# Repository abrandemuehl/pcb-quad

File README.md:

# UIUC ECE395 PCB Quadcopter Project
The goal of the project was to design a quadcopter with a PCB frame and as many
parts as possible soldered directly onto it. We put an STM32F4, and a BNO055 
IMU onto the board, and purchased external ESC's for the motors.

### Results
Due to difficulties with a parts order through the school, we were not able to 
sufficiently test the hardware before a final version was due. We missed a pull
up resistor on the BNO055's NRESET pin, causing it to constantly be in a state 
of reset, and making it unusable. We fixed it by taping our breakout board IMU 
onto the board, and connecting the necessary wires. After that, we had working 
hardware, but were not able to finish tuning the quadcopter before a failure 
broke one of the motors. We did not have a tuning rig, so we were forced to tune
it by attempting to hover at about floor level. Eventually, one of the motors 
that we used failed, ending the project with working hardware and software, but
incomplete tuning.

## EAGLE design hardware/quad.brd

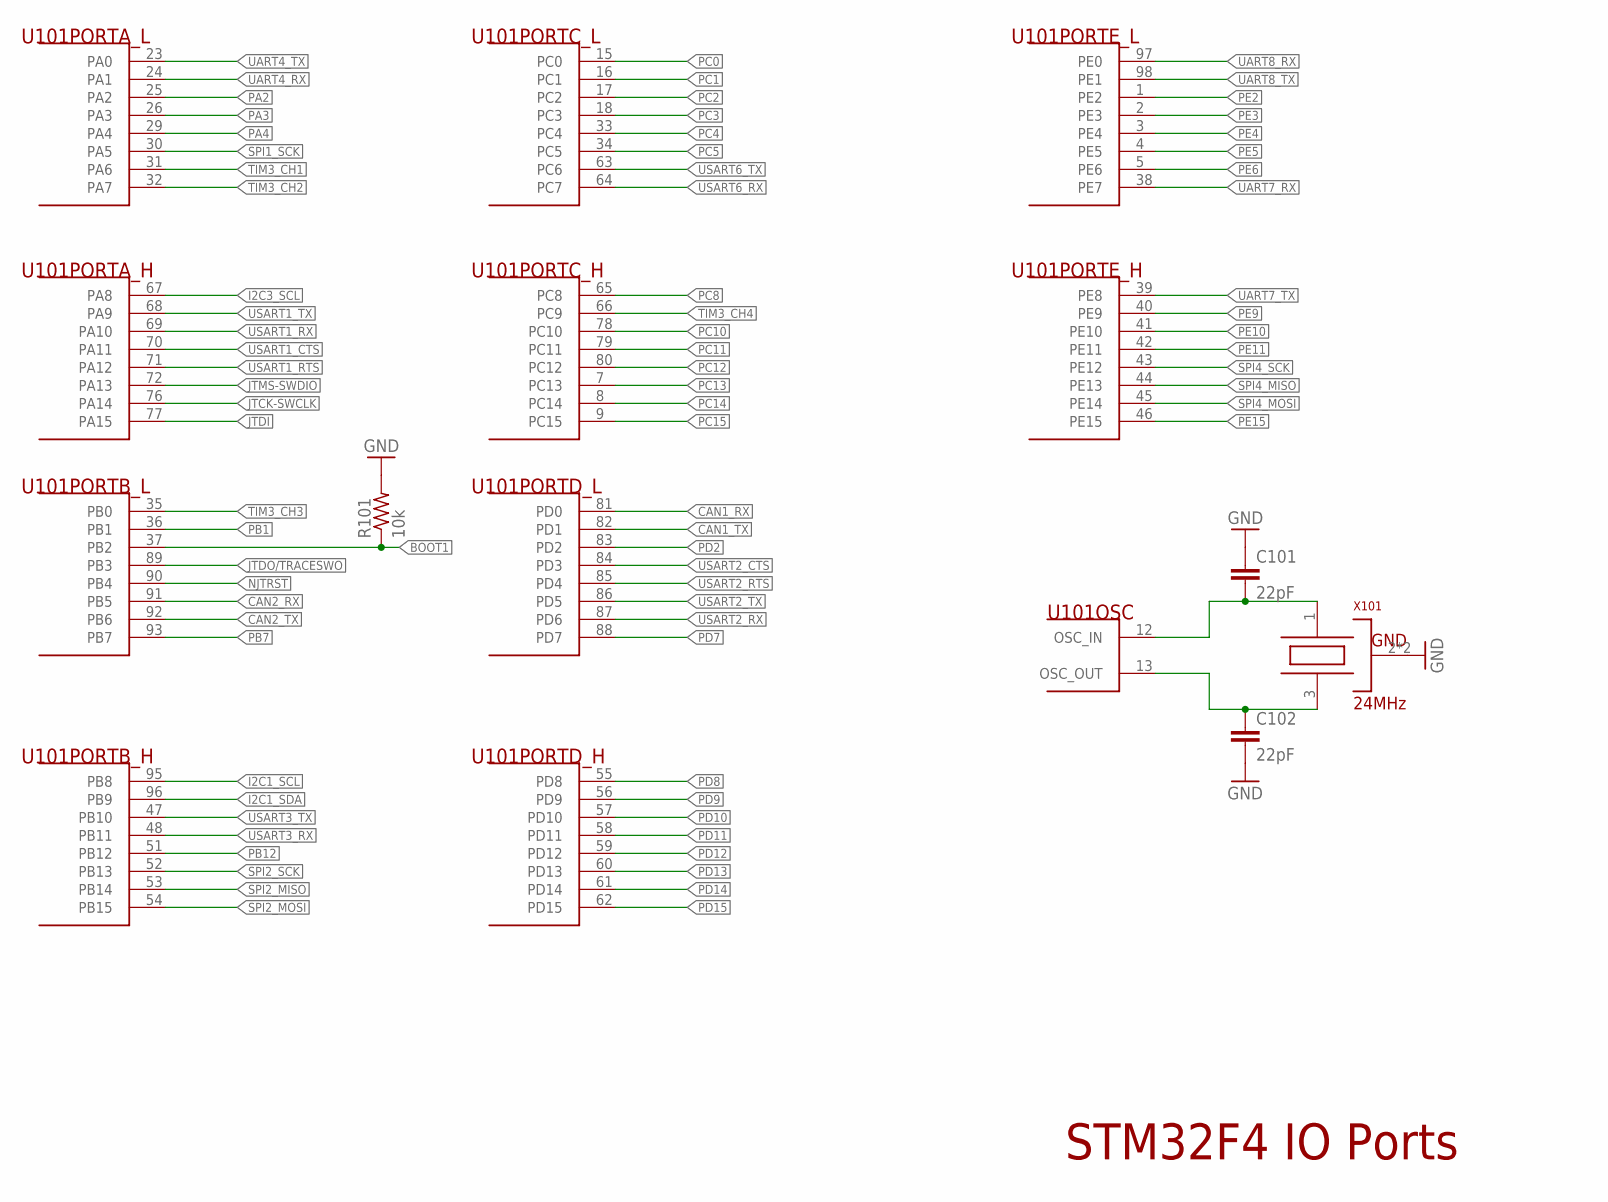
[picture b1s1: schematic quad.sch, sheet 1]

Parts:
C101, C102: 22pF; C0603
R101: 10k; R0603
U101: STM32F427VGT6; LQFP-100
X101: 24MHz; OSC3.2X2.5

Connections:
BOOT1: R101.1, U101.37 (PB2)
CAN1_RX: U101.81 (PD0)
CAN1_TX: U101.82 (PD1)
CAN2_RX: U101.91 (PB5)
CAN2_TX: U101.92 (PB6)
GND: C101.1, C102.2, R101.2, X101.2 (GND), X101.4 (GND); also elsewhere on the board
I2C1_SCL: U101.95 (PB8); also elsewhere on the board
I2C1_SDA: U101.96 (PB9); also elsewhere on the board
I2C3_SCL: U101.67 (PA8)
JTCK-SWCLK: U101.76 (PA14)
JTDI: U101.77 (PA15)
JTDO/TRACESWO: U101.89 (PB3)
JTMS-SWDIO: U101.72 (PA13)
NJTRST: U101.90 (PB4)
OSC_IN: C101.2, U101.12 (OSC_IN), X101.1 (OSC1)
OSC_OUT: C102.1, U101.13 (OSC_OUT), X101.3 (OSC2)
PA2: U101.25 (PA2)
PA3: U101.26 (PA3)
PA4: U101.29 (PA4)
PB1: U101.36 (PB1)
PB7: U101.93 (PB7)
PB12: U101.51 (PB12)
PC0: U101.15 (PC0)
PC1: U101.16 (PC1)
PC2: U101.17 (PC2)
PC3: U101.18 (PC3)
PC4: U101.33 (PC4)
PC5: U101.34 (PC5)
PC8: U101.65 (PC8)
PC10: U101.78 (PC10)
PC11: U101.79 (PC11)
PC12: U101.80 (PC12)
PC13: U101.7 (PC13)
PC14: U101.8 (PC14)
PC15: U101.9 (PC15)
PD2: U101.83 (PD2); also elsewhere on the board
PD7: U101.88 (PD7)
PD8: U101.55 (PD8)
PD9: U101.56 (PD9)
PD10: U101.57 (PD10)
PD11: U101.58 (PD11)
PD12: U101.59 (PD12)
PD13: U101.60 (PD13)
PD14: U101.61 (PD14)
PD15: U101.62 (PD15)
PE2: U101.1 (PE2)
PE3: U101.2 (PE3)
PE4: U101.3 (PE4)
PE5: U101.4 (PE5)
PE6: U101.5 (PE6)
PE9: U101.40 (PE9)
PE10: U101.41 (PE10)
PE11: U101.42 (PE11)
PE15: U101.46 (PE15)
SPI1_SCK: U101.30 (PA5)
SPI2_MISO: U101.53 (PB14)
SPI2_MOSI: U101.54 (PB15)
SPI2_SCK: U101.52 (PB13)
SPI4_MISO: U101.44 (PE13)
SPI4_MOSI: U101.45 (PE14)
SPI4_SCK: U101.43 (PE12)
TIM3_CH1: U101.31 (PA6); also elsewhere on the board
TIM3_CH2: U101.32 (PA7); also elsewhere on the board
TIM3_CH3: U101.35 (PB0); also elsewhere on the board
TIM3_CH4: U101.66 (PC9); also elsewhere on the board
UART4_RX: U101.24 (PA1)
UART4_TX: U101.23 (PA0)
UART7_RX: U101.38 (PE7)
UART7_TX: U101.39 (PE8)
UART8_RX: U101.97 (PE0)
UART8_TX: U101.98 (PE1)
USART1_CTS: U101.70 (PA11)
USART1_RTS: U101.71 (PA12)
USART1_RX: U101.69 (PA10); also elsewhere on the board
USART1_TX: U101.68 (PA9); also elsewhere on the board
USART2_CTS: U101.84 (PD3)
USART2_RTS: U101.85 (PD4)
USART2_RX: U101.87 (PD6)
USART2_TX: U101.86 (PD5)
USART3_RX: U101.48 (PB11); also elsewhere on the board
USART3_TX: U101.47 (PB10); also elsewhere on the board
USART6_RX: U101.64 (PC7)
USART6_TX: U101.63 (PC6)

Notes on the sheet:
STM32F4 IO Ports

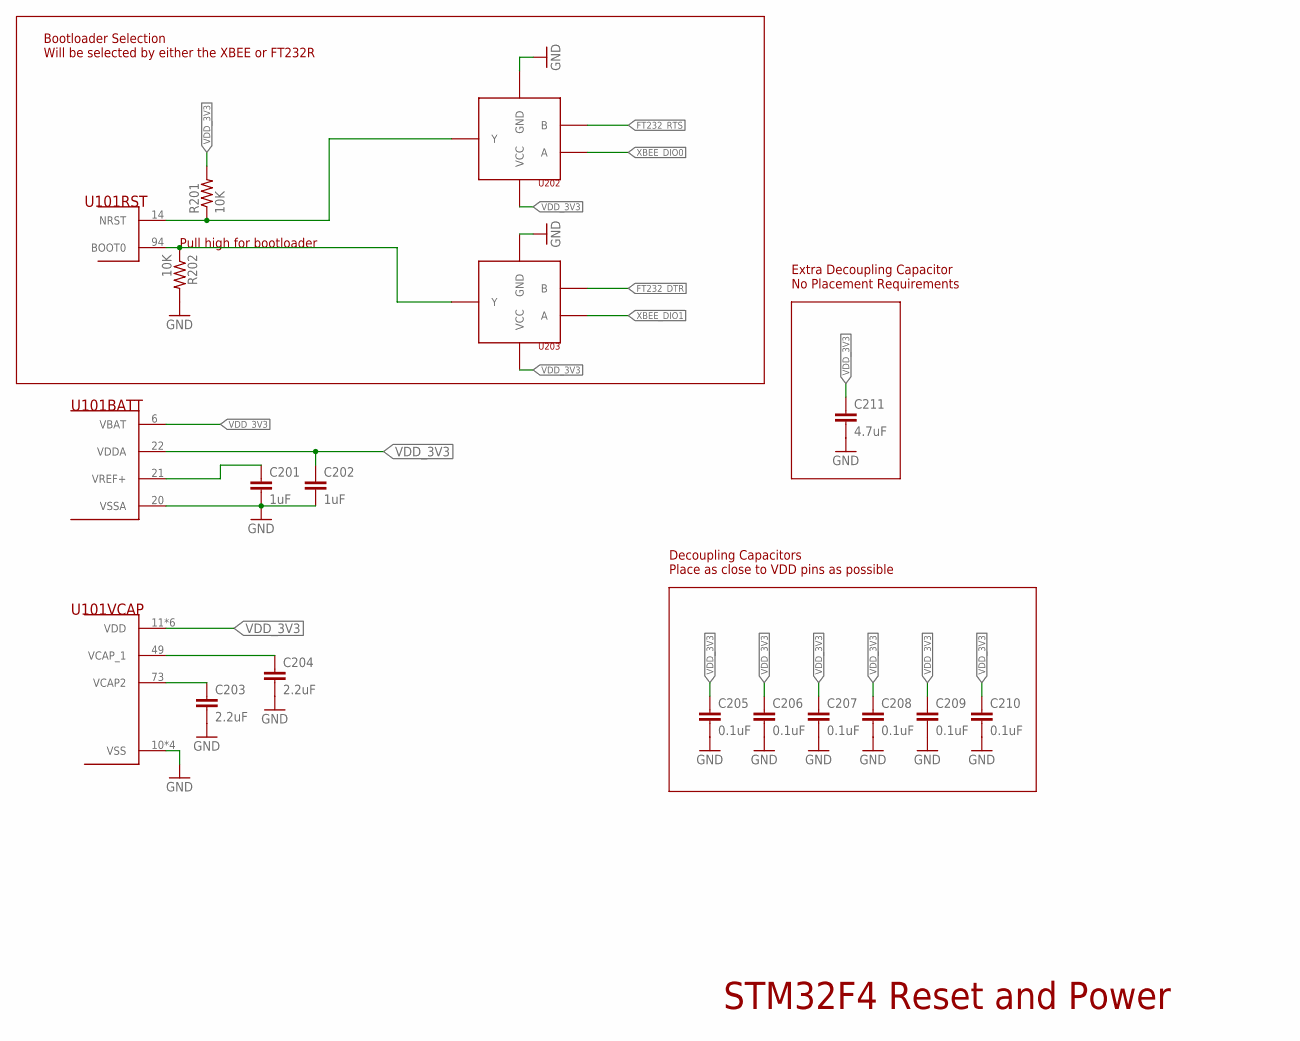
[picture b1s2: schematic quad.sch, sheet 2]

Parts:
C201, C202: 1uF; C0603
C203, C204: 2.2uF; C0603
C205, C206, C207, C208, C209, C210: 0.1uF; C0603
C211: 4.7uF; C0603
R201, R202: 10K; R0603
U101: STM32F427VGT6; LQFP-100
U202: AND_GATE; SOT23-5L
U203: SN74AHC1G32DBVR; SOT23-5L

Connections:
BOOT0: R202.1, U101.94 (BOOT0), U203.4 (Y)
FT232_DTR: U203.2 (B); also elsewhere on the board
FT232_RTS: U202.2 (B); also elsewhere on the board
GND: C201.2, C202.2, C203.2, C204.2, C205.2, C206.2, C207.2, C208.2, C209.2, C210.2, C211.2, R202.2, U101.10 (VSS), U101.20 (VSSA), U101.27 (VSS), U101.74 (VSS), U101.99 (VSS), U202.3 (GND), U203.3 (GND); also elsewhere on the board
NRST: R201.1, U101.14 (NRST), U202.4 (Y)
VCAP2: C203.1, U101.73 (VCAP2)
VCAP_1: C204.1, U101.49 (VCAP_1)
VDD_3V3: C201.1, C202.1, C205.1, C206.1, C207.1, C208.1, C209.1, C210.1, C211.1, R201.2, U101.6 (VBAT), U101.11 (VDD), U101.19 (VDD), U101.21 (VREF+), U101.22 (VDDA), U101.28 (VDD), U101.50 (VDD), U101.75 (VDD), U101.100 (VDD), U202.5 (VCC), U203.5 (VCC); also elsewhere on the board
XBEE_DIO0: U202.1 (A); also elsewhere on the board
XBEE_DIO1: U203.1 (A); also elsewhere on the board

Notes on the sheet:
STM32F4 Reset and Power
Decoupling Capacitors Place as close to VDD pins as possible
Extra Decoupling Capacitor No Placement Requirements
Pull high for bootloader
Bootloader Selection Will be selected by either the XBEE or FT232R

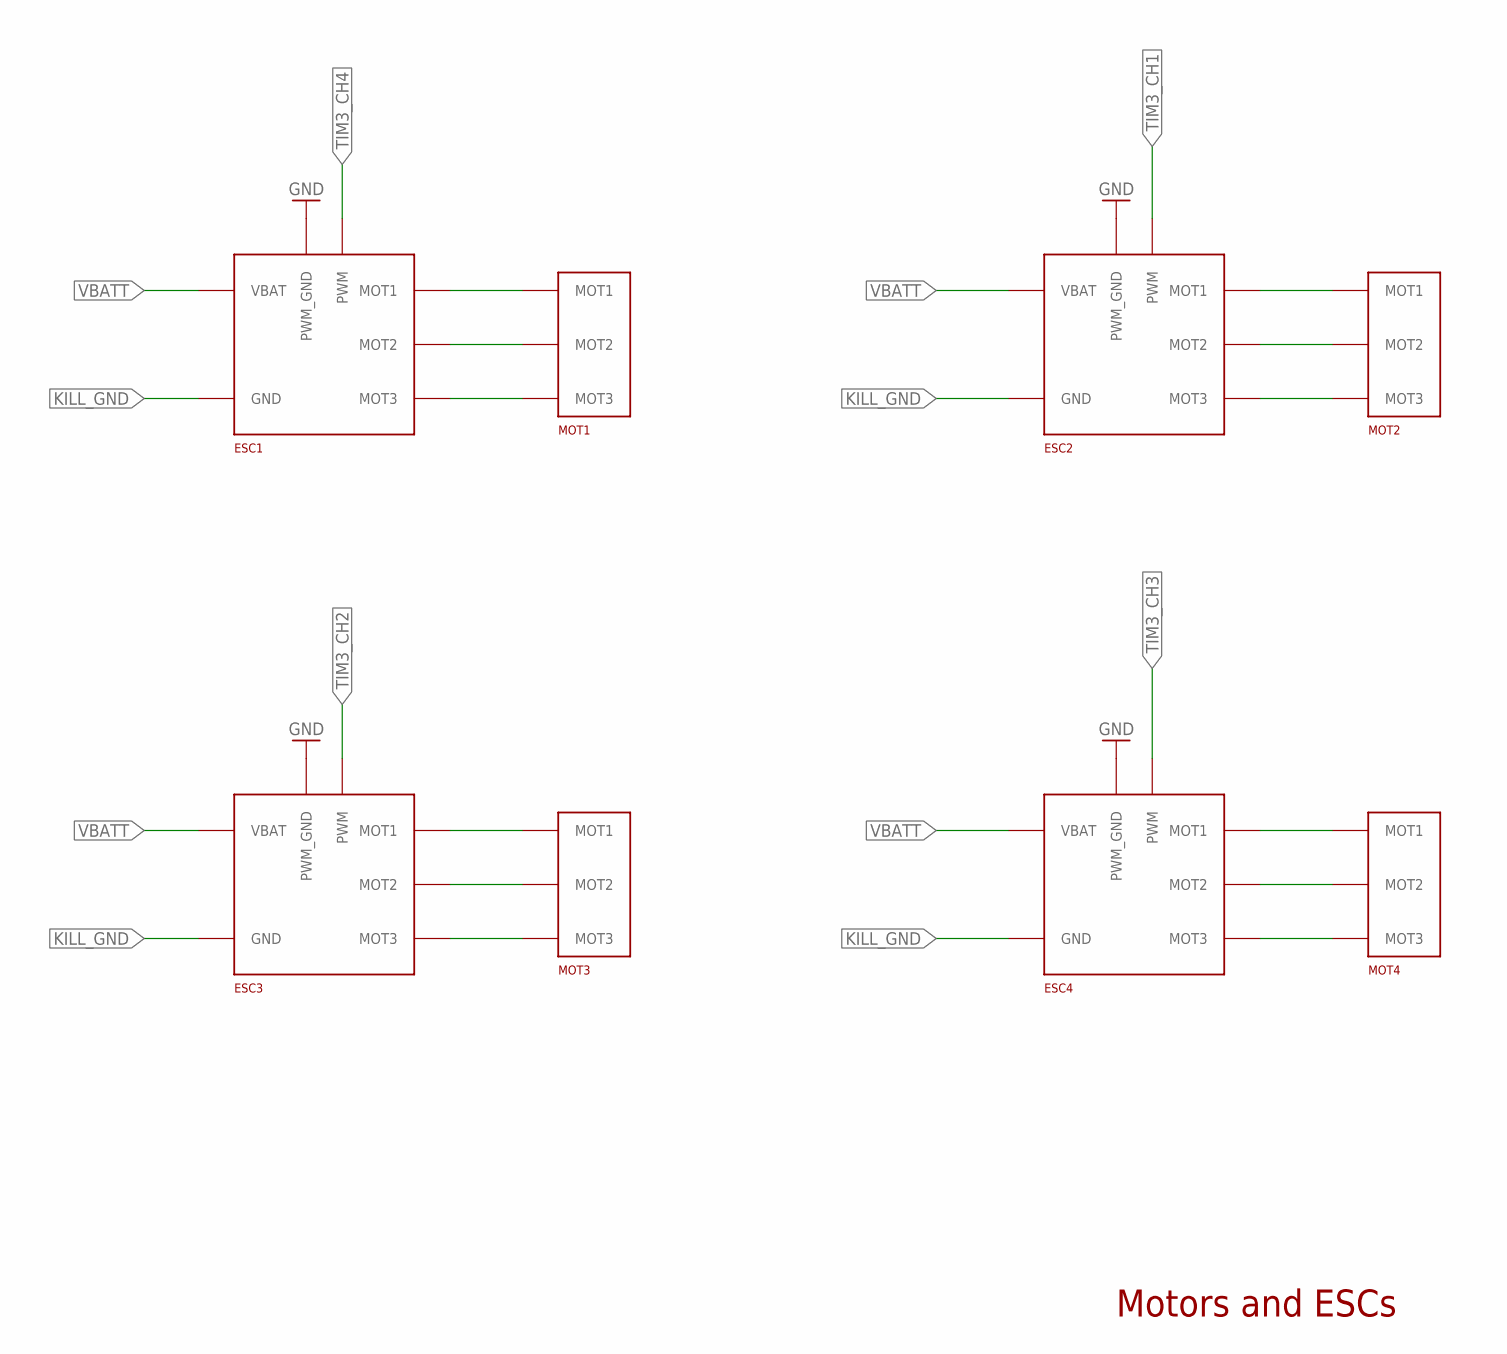
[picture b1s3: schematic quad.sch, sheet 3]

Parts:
ESC1, ESC2, ESC3, ESC4: AFRO_ESC
MOT1, MOT2, MOT3, MOT4: MOTOR

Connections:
GND: ESC1.PWM_GND, ESC2.PWM_GND, ESC3.PWM_GND, ESC4.PWM_GND; also elsewhere on the board
KILL_GND: ESC1.GND, ESC2.GND, ESC3.GND, ESC4.GND; also elsewhere on the board
MOT1_1: ESC1.MOT1, MOT1.MOT1
MOT1_2: ESC1.MOT2, MOT1.MOT2
MOT1_3: ESC1.MOT3, MOT1.MOT3
MOT2_1: ESC2.MOT1, MOT2.MOT1
MOT_2_2: ESC2.MOT2, MOT2.MOT2
MOT_2_3: ESC2.MOT3, MOT2.MOT3
MOT_3_1: ESC3.MOT1, MOT3.MOT1
MOT_3_2: ESC3.MOT2, MOT3.MOT2
MOT_3_3: ESC3.MOT3, MOT3.MOT3
MOT_4_1: ESC4.MOT1, MOT4.MOT1
MOT_4_2: ESC4.MOT2, MOT4.MOT2
MOT_4_3: ESC4.MOT3, MOT4.MOT3
TIM3_CH1: ESC2.PWM; also elsewhere on the board
TIM3_CH2: ESC3.PWM; also elsewhere on the board
TIM3_CH3: ESC4.PWM; also elsewhere on the board
TIM3_CH4: ESC1.PWM; also elsewhere on the board
VBATT: ESC1.VBATT (VBAT), ESC2.VBATT (VBAT), ESC3.VBATT (VBAT), ESC4.VBATT (VBAT); also elsewhere on the board

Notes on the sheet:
Motors and ESCs

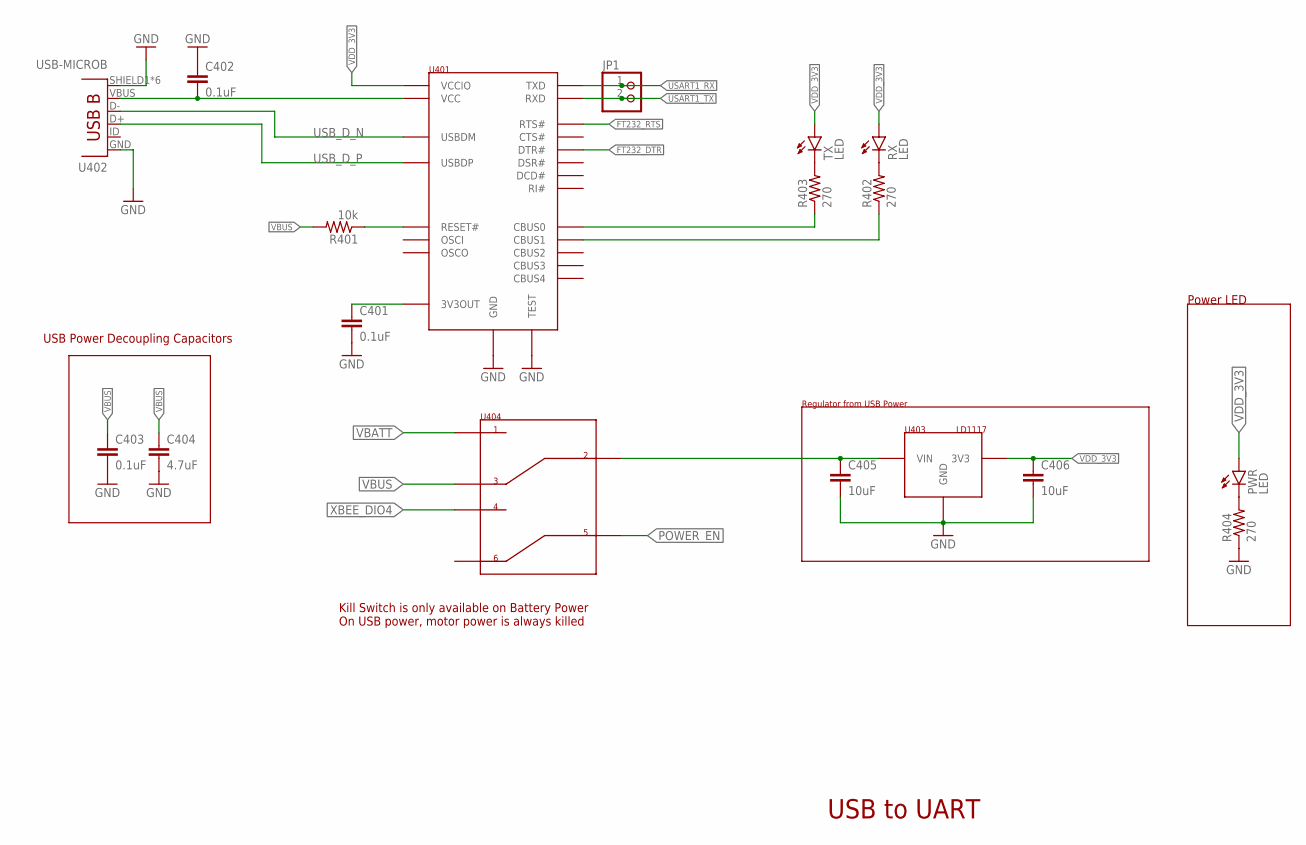
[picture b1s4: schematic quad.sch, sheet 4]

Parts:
C401, C402, C403: 0.1uF; C0603
C404: 4.7uF; C0603
C405, C406: 10uF; C0603
JP1: PINHD-1X2; 1X02
PWR: LED; LED-0603
R401: 10k; R0603
R402, R403, R404: 270; R0603
RX: LED; LED-0603
TX: LED; LED-0603
U401: FT232R; SSOP28
U402: USB-MICROB; USB-B-MICRO-SMD
U403: LD1117; SOT223
U404: MFS201N-16-Z

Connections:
FT232_DTR: U401.2 (DTR#); also elsewhere on the board
FT232_RTS: U401.3 (RTS#); also elsewhere on the board
GND: C401.2, C402.1, C403.2, C404.2, C405.2, C406.2, R404.1, U401.7 (GND), U401.18 (GND), U401.21 (GND), U401.25 (GND), U401.26 (TEST), U402.GND, U402.SHIELD1 (SHIELD), U402.SHIELD2 (SHIELD), U402.SHIELD3 (SHIELD), U402.SHIELD4 (SHIELD), U402.SHIELD5 (SHIELD), U402.SHIELD6 (SHIELD), U403.1 (GND); also elsewhere on the board
unnamed: R401.1, U401.19 (RESET#)
unnamed: C401.1, U401.17 (3V3OUT)
unnamed: R403.1, U401.23 (CBUS0)
unnamed: R402.1, U401.22 (CBUS1)
unnamed: R402.2, RX.C
unnamed: R403.2, TX.C
unnamed: PWR.C, R404.2
POWER_EN: U404.5; also elsewhere on the board
PWR: C405.1, U403.3 (VIN), U404.2
USART1_RX: JP1.1, U401.1 (TXD); also elsewhere on the board
USART1_TX: JP1.2, U401.5 (RXD); also elsewhere on the board
USB_D_N: U401.16 (USBDM), U402.D-
USB_D_P: U401.15 (USBDP), U402.D+
VBATT: U404.1; also elsewhere on the board
VBUS: C402.2, C403.1, C404.1, R401.2, U401.20 (VCC), U402.VBUS, U404.3
VDD_3V3: C406.1, PWR.A, RX.A, TX.A, U401.4 (VCCIO), U403.2 (3V3), U403.4 (3V3); also elsewhere on the board
XBEE_DIO4: U404.4; also elsewhere on the board

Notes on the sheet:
USB to UART
USB Power Decoupling Capacitors
Regulator from USB Power
Kill Switch is only available on Battery Power On USB power, motor power is always killed
Power LED

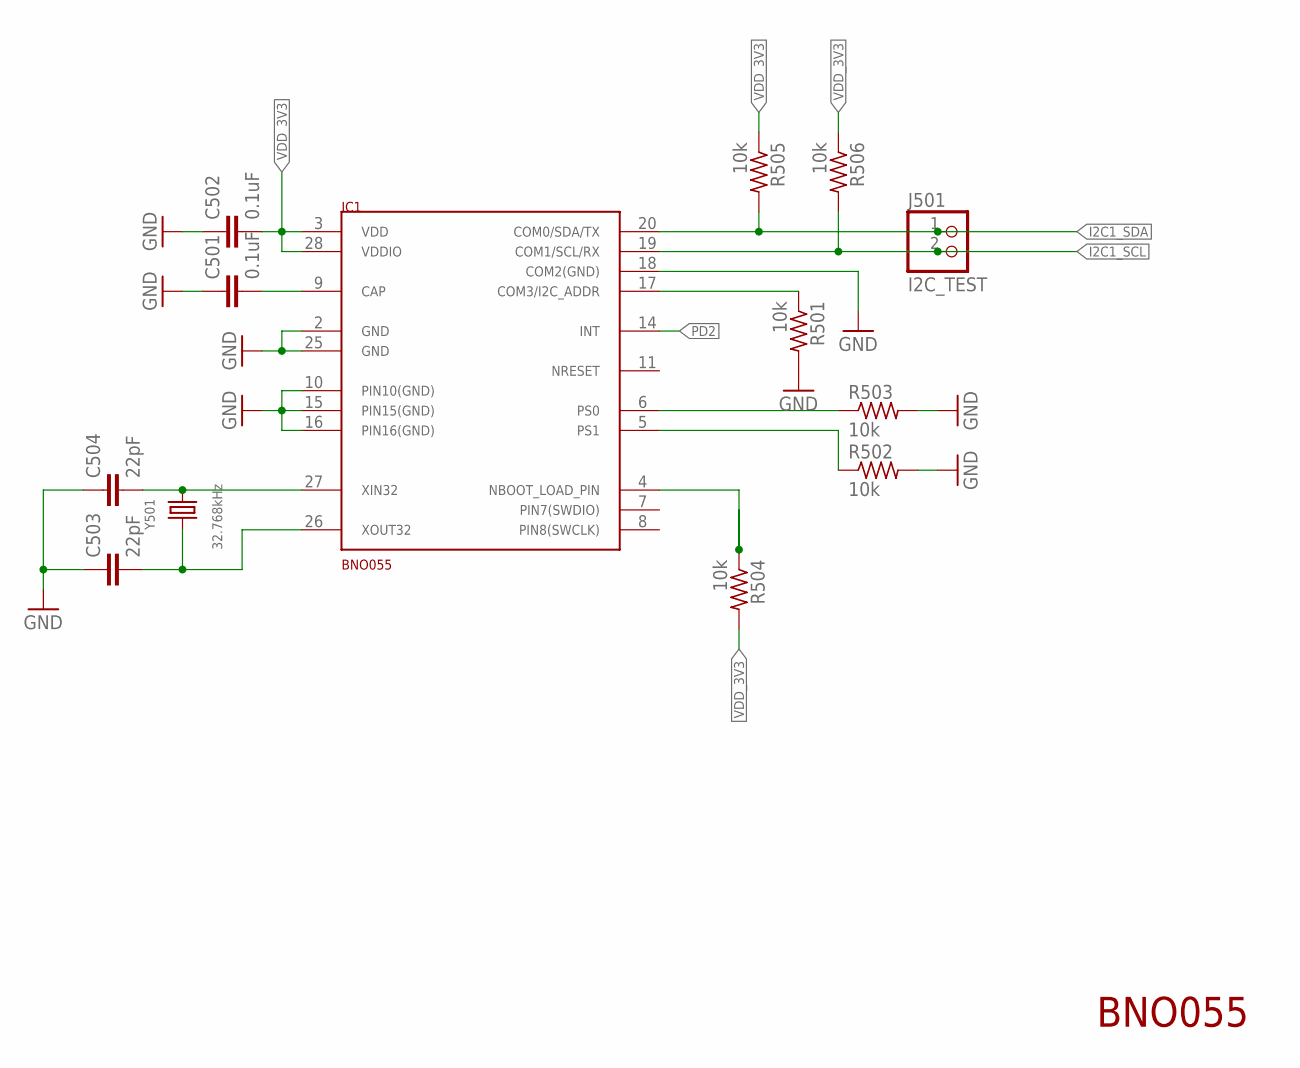
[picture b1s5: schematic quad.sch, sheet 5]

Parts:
C501, C502: 0.1uF; C0603
C503, C504: 22pF; C0603
IC1: BNO055; LGA-28_3.80X5.20/0.5
J501: I2C_TEST; 1X02
R501, R502, R503, R504, R505, R506: 10k; R0603
Y501: 32.768kHz; ABS25

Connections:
GND: C501.1, C502.1, C503.1, C504.1, IC1.2, IC1.10, IC1.15, IC1.16, IC1.18, IC1.25, R501.2, R502.2, R503.2; also elsewhere on the board
I2C1_SCL: IC1.19, J501.2, R506.2; also elsewhere on the board
I2C1_SDA: IC1.20, J501.1, R505.2; also elsewhere on the board
unnamed: C501.2, IC1.9
unnamed: C504.2, IC1.27, Y501.4 (2)
unnamed: C503.2, IC1.26, Y501.1
unnamed: IC1.17, R501.1
unnamed: IC1.6, R503.1
unnamed: IC1.5, R502.1
unnamed: IC1.4, R504.1
PD2: IC1.14; also elsewhere on the board
VDD_3V3: C502.2, IC1.3, IC1.28, R504.2, R505.1, R506.1; also elsewhere on the board

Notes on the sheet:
BNO055

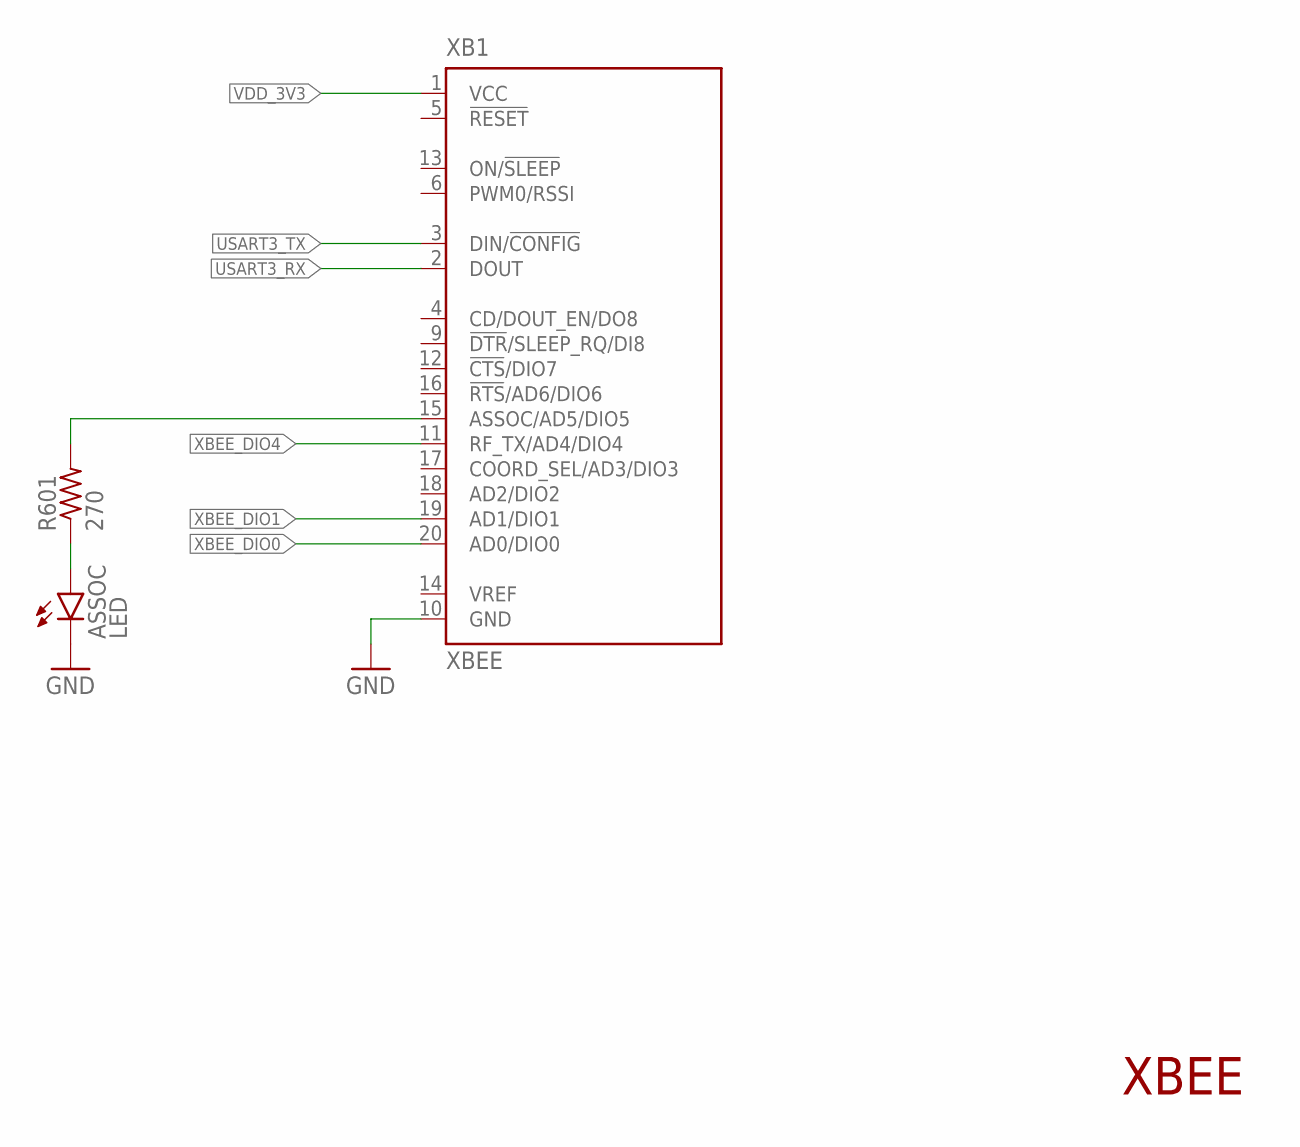
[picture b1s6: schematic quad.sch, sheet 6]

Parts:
ASSOC: LED; LED-0603
R601: 270; R0603
XB1: XBEE

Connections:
GND: ASSOC.C, XB1.10 (GND); also elsewhere on the board
unnamed: ASSOC.A, R601.1
unnamed: R601.2, XB1.15 (ASSOC/AD5/DIO5)
USART3_RX: XB1.2 (DOUT); also elsewhere on the board
USART3_TX: XB1.3 (DIN/!CONFIG); also elsewhere on the board
VDD_3V3: XB1.1 (VCC); also elsewhere on the board
XBEE_DIO0: XB1.20 (AD0/DIO0); also elsewhere on the board
XBEE_DIO1: XB1.19 (AD1/DIO1); also elsewhere on the board
XBEE_DIO4: XB1.11 (RF_TX/AD4/DIO4); also elsewhere on the board

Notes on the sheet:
XBEE

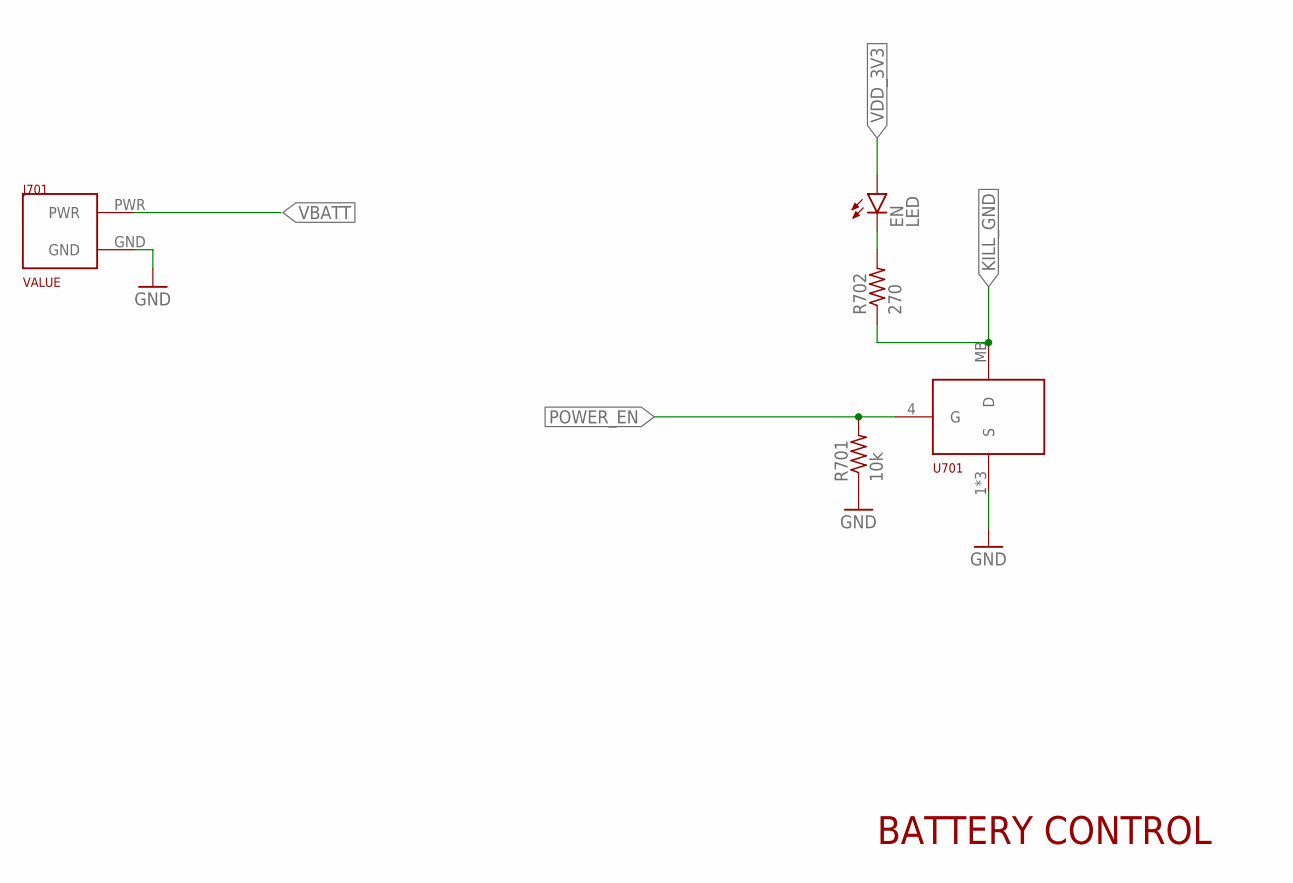
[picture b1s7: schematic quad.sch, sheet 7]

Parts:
EN: LED; LED-0603
J701: XT60
R701: 10k; R0603
R702: 270; R0603
U701: PSMN9RS-30YLC; SOT669

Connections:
GND: J701.GND, R701.1, U701.1 (S), U701.2 (S), U701.3 (S); also elsewhere on the board
KILL_GND: R702.1, U701.MB (D); also elsewhere on the board
unnamed: EN.C, R702.2
POWER_EN: R701.2, U701.4 (G); also elsewhere on the board
VBATT: J701.PWR; also elsewhere on the board
VDD_3V3: EN.A; also elsewhere on the board

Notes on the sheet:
BATTERY CONTROL

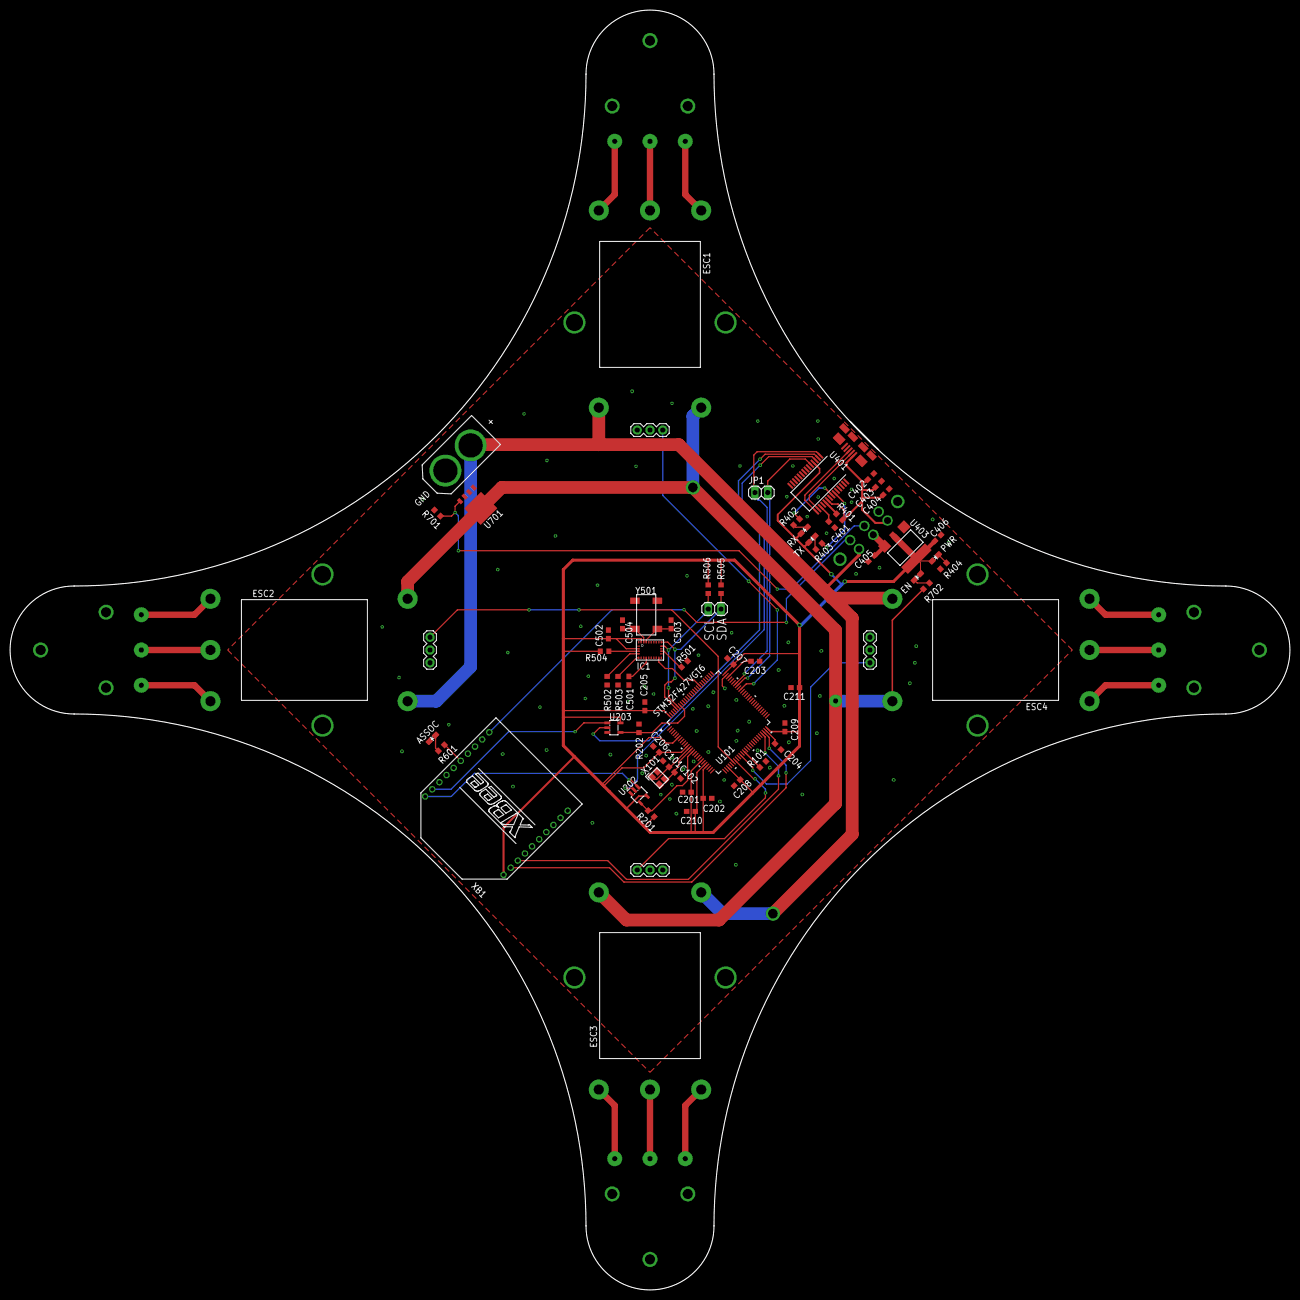
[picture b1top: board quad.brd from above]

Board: 2 copper layers, 254.0 x 254.0 mm, 67 parts (0 on the bottom side), 61 nets.

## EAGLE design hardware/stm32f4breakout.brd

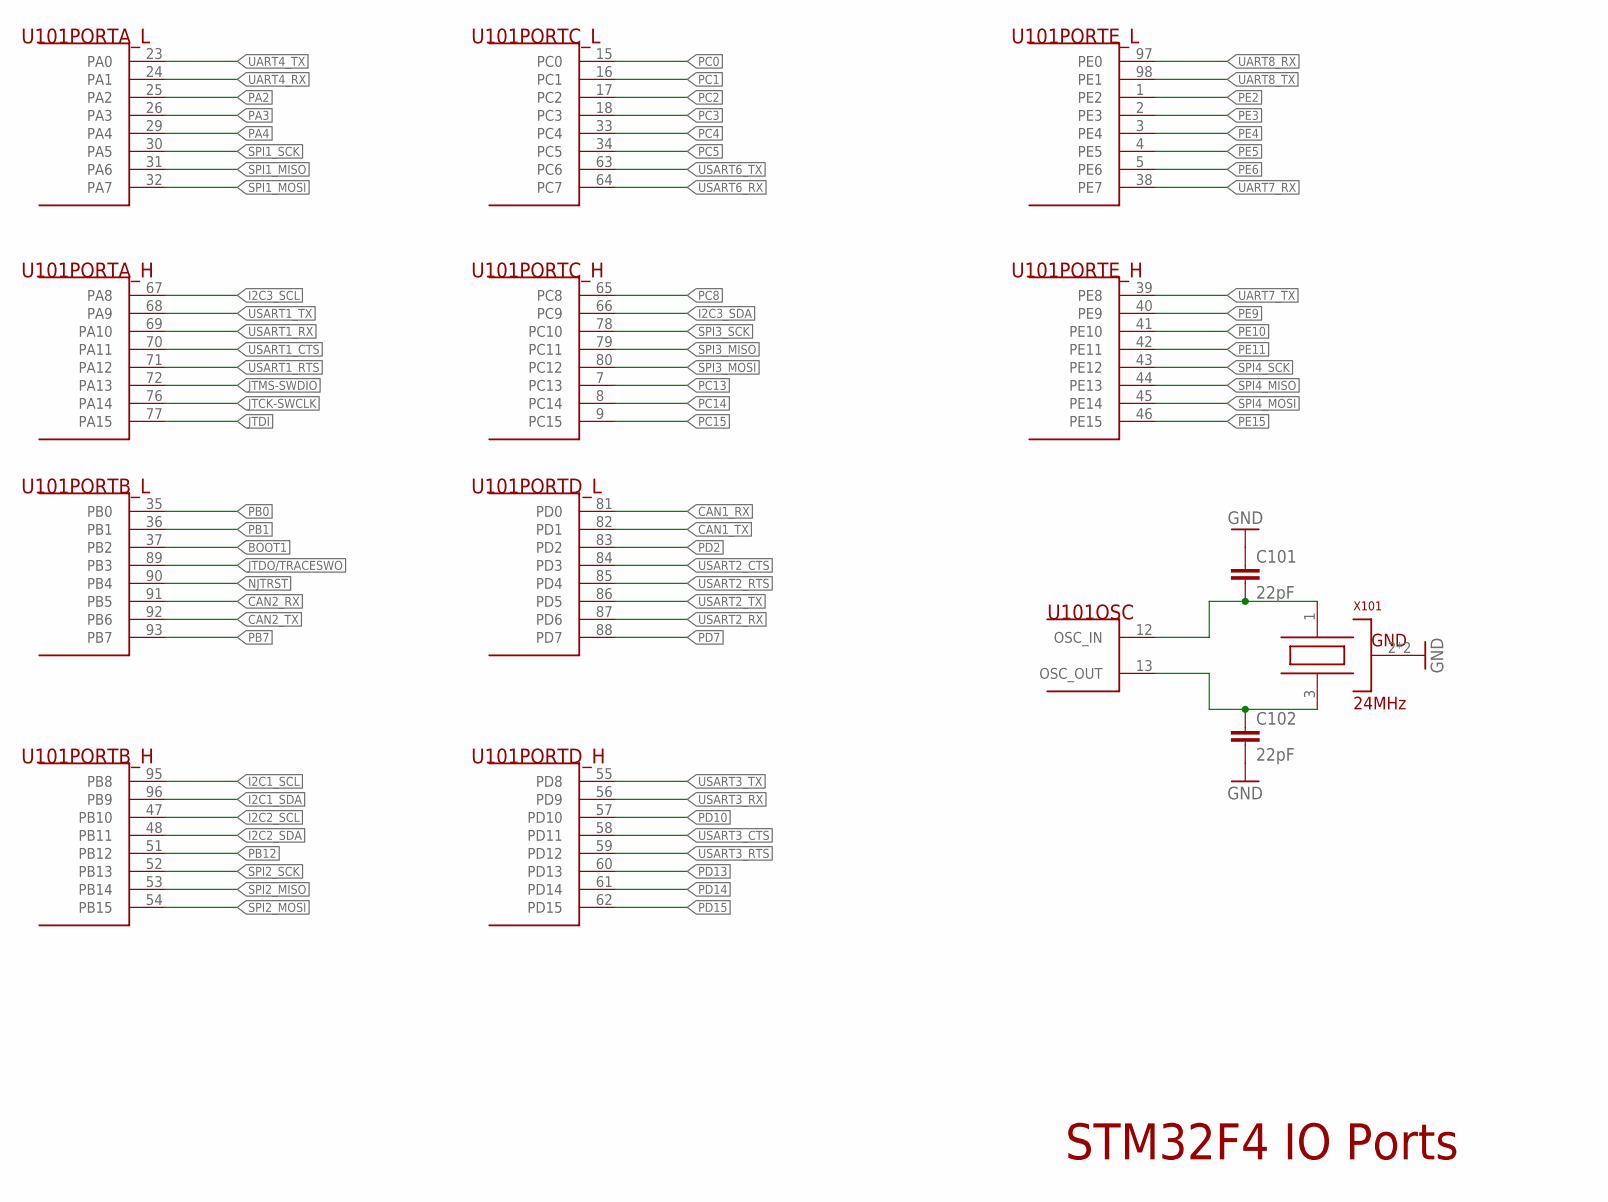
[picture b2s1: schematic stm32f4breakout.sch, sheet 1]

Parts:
C101, C102: 22pF; C0603
U101: STM32F427VGT6; LQFP-100
X101: 24MHz; OSC3.2X2.5

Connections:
BOOT1: U101.37 (PB2); also elsewhere on the board
CAN1_RX: U101.81 (PD0); also elsewhere on the board
CAN1_TX: U101.82 (PD1); also elsewhere on the board
CAN2_RX: U101.91 (PB5); also elsewhere on the board
CAN2_TX: U101.92 (PB6); also elsewhere on the board
GND: C101.1, C102.2, X101.2 (GND), X101.4 (GND); also elsewhere on the board
I2C1_SCL: U101.95 (PB8); also elsewhere on the board
I2C1_SDA: U101.96 (PB9); also elsewhere on the board
I2C2_SCL: U101.47 (PB10); also elsewhere on the board
I2C2_SDA: U101.48 (PB11); also elsewhere on the board
I2C3_SCL: U101.67 (PA8); also elsewhere on the board
I2C3_SDA: U101.66 (PC9); also elsewhere on the board
JTCK-SWCLK: U101.76 (PA14); also elsewhere on the board
JTDI: U101.77 (PA15); also elsewhere on the board
JTDO/TRACESWO: U101.89 (PB3); also elsewhere on the board
JTMS-SWDIO: U101.72 (PA13); also elsewhere on the board
NJTRST: U101.90 (PB4); also elsewhere on the board
OSC_IN: C101.2, U101.12 (OSC_IN), X101.1 (OSC1)
OSC_OUT: C102.1, U101.13 (OSC_OUT), X101.3 (OSC2)
PA2: U101.25 (PA2); also elsewhere on the board
PA3: U101.26 (PA3); also elsewhere on the board
PA4: U101.29 (PA4); also elsewhere on the board
PB0: U101.35 (PB0); also elsewhere on the board
PB1: U101.36 (PB1); also elsewhere on the board
PB7: U101.93 (PB7); also elsewhere on the board
PB12: U101.51 (PB12); also elsewhere on the board
PC0: U101.15 (PC0); also elsewhere on the board
PC1: U101.16 (PC1); also elsewhere on the board
PC2: U101.17 (PC2); also elsewhere on the board
PC3: U101.18 (PC3); also elsewhere on the board
PC4: U101.33 (PC4); also elsewhere on the board
PC5: U101.34 (PC5); also elsewhere on the board
PC8: U101.65 (PC8); also elsewhere on the board
PC13: U101.7 (PC13); also elsewhere on the board
PC14: U101.8 (PC14); also elsewhere on the board
PC15: U101.9 (PC15); also elsewhere on the board
PD2: U101.83 (PD2); also elsewhere on the board
PD7: U101.88 (PD7); also elsewhere on the board
PD10: U101.57 (PD10); also elsewhere on the board
PD13: U101.60 (PD13); also elsewhere on the board
PD14: U101.61 (PD14); also elsewhere on the board
PD15: U101.62 (PD15); also elsewhere on the board
PE2: U101.1 (PE2); also elsewhere on the board
PE3: U101.2 (PE3); also elsewhere on the board
PE4: U101.3 (PE4); also elsewhere on the board
PE5: U101.4 (PE5); also elsewhere on the board
PE6: U101.5 (PE6); also elsewhere on the board
PE9: U101.40 (PE9); also elsewhere on the board
PE10: U101.41 (PE10); also elsewhere on the board
PE11: U101.42 (PE11); also elsewhere on the board
PE15: U101.46 (PE15); also elsewhere on the board
SPI1_MISO: U101.31 (PA6); also elsewhere on the board
SPI1_MOSI: U101.32 (PA7); also elsewhere on the board
SPI1_SCK: U101.30 (PA5); also elsewhere on the board
SPI2_MISO: U101.53 (PB14); also elsewhere on the board
SPI2_MOSI: U101.54 (PB15); also elsewhere on the board
SPI2_SCK: U101.52 (PB13); also elsewhere on the board
SPI3_MISO: U101.79 (PC11); also elsewhere on the board
SPI3_MOSI: U101.80 (PC12); also elsewhere on the board
SPI3_SCK: U101.78 (PC10); also elsewhere on the board
SPI4_MISO: U101.44 (PE13); also elsewhere on the board
SPI4_MOSI: U101.45 (PE14); also elsewhere on the board
SPI4_SCK: U101.43 (PE12); also elsewhere on the board
UART4_RX: U101.24 (PA1); also elsewhere on the board
UART4_TX: U101.23 (PA0); also elsewhere on the board
UART7_RX: U101.38 (PE7); also elsewhere on the board
UART7_TX: U101.39 (PE8); also elsewhere on the board
UART8_RX: U101.97 (PE0); also elsewhere on the board
UART8_TX: U101.98 (PE1); also elsewhere on the board
USART1_CTS: U101.70 (PA11); also elsewhere on the board
USART1_RTS: U101.71 (PA12); also elsewhere on the board
USART1_RX: U101.69 (PA10); also elsewhere on the board
USART1_TX: U101.68 (PA9); also elsewhere on the board
USART2_CTS: U101.84 (PD3); also elsewhere on the board
USART2_RTS: U101.85 (PD4); also elsewhere on the board
USART2_RX: U101.87 (PD6); also elsewhere on the board
USART2_TX: U101.86 (PD5); also elsewhere on the board
USART3_CTS: U101.58 (PD11); also elsewhere on the board
USART3_RTS: U101.59 (PD12); also elsewhere on the board
USART3_RX: U101.56 (PD9); also elsewhere on the board
USART3_TX: U101.55 (PD8); also elsewhere on the board
USART6_RX: U101.64 (PC7); also elsewhere on the board
USART6_TX: U101.63 (PC6); also elsewhere on the board

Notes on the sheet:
STM32F4 IO Ports
